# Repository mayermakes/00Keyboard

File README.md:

# 00Keyboard
an open source ortholinear BLE keyboard. from scratch, including Firmware, video on element14presents
you can find the source (freecad project) for the keyset on Community.element14.com / LINK
Github says the file is to big to upload here... uuughh

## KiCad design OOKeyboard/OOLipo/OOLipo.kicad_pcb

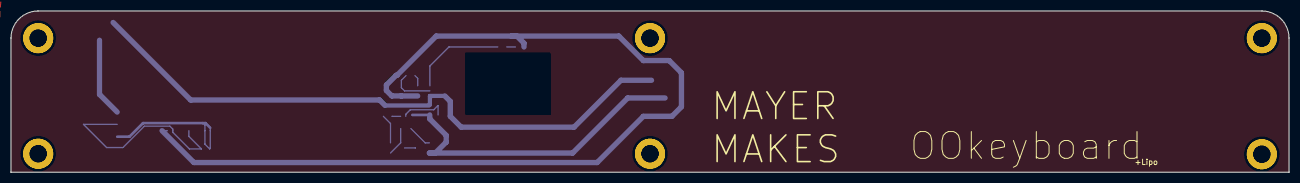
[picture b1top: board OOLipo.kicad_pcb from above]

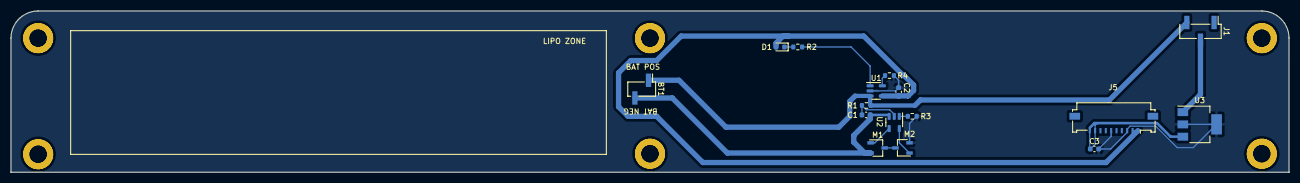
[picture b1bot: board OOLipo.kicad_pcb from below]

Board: 2 copper layers, 238.8 x 30.1 mm, 22 parts (16 on the bottom side), 14 nets.

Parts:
BT1: LIPO; PinHeader_1x02_P2.54mm_Vertical_SMD_Pin1Left
C1, C3: 0.1uF; C_0603_1608Metric
C2: 4,7uF; C_0603_1608Metric
D1: LED; LED_0603_1608Metric
H1, H2, H3, H4, H5, H6: MountingHole_Pad; MountingHole_3.2mm_M3_DIN965_Pad
J1: power Switch; PinHeader_1x03_P2.54mm_Vertical_SMD_Pin1Left
J5: 10x1mm FFC/FPC; Molex_200528-0100_1x10-1MP_P1.00mm_Horizontal
M1, M2: DMG6968U-7_single; TSOT-23
R1: 330; R_0603_1608Metric
R2: 150; R_0603_1608Metric
R3: 2k7; R_0603_1608Metric
R4: 10k/2k; R_0603_1608Metric
U1: MCP73831-2-OT; SOT-23-5
U2: AP9101CK; SOT-23-5
U3: MCP1825S; SOT-223-3_TabPin2

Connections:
+3V3: C3.1, J5.9, J5.10, U3.3 (VO)
/CO: M2.1 (G), U2.5 (CO)
/DO: M1.1 (G), U2.4 (DO)
/VBUS: C2.1, D1.2 (A), J5.1, J5.2, U1.4 (VDD)
/bat-: BT1.2 (-), C1.2, M1.2 (S), U2.3 (VSS)
GND: C2.2, C3.2, H1.1, H2.1, H3.1, H4.1, H5.1, H6.1, J5.3, J5.6, M2.2 (S), R3.2, R4.1, U1.2 (VSS), U3.2 (GND)
HV_CHR: J1.2, U3.1 (VI)
unnamed: BT1.1 (+), J1.3, R1.2, U1.3 (VBAT)
unnamed: D1.1 (K), R2.2
unnamed: M1.3 (D), M2.3 (D)
unnamed: R4.2, U1.5 (PROG)
unnamed: R2.1, U1.1 (STAT)
unnamed: C1.1, R1.1, U2.2 (VDD)
unnamed: R3.1, U2.1 (VM)

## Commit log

2023-08-25 initial upload
    only opne prototype done so far
    use schottky diodes on the switches and zero ohm resistors FYI
